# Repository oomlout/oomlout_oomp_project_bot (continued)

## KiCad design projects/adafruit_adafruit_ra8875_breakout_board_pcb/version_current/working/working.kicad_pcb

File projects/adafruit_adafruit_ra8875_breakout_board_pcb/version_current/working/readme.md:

# OOMP Project  
## Adafruit-RA8875-Breakout-Board-PCB  by adafruit  
  
oomp key: oomp_projects_flat_adafruit_adafruit_ra8875_breakout_board_pcb  
(snippet of original readme)  
  
-- Adafruit RA8875 Driver Board for 40-pin TFT Touch Displays - 800x480 Max PCB  
  
<a href="http://www.adafruit.com/products/1590"><br/>  
Click here to purchase one from the Adafruit shop</a>  
  
PCB files for the Adafruit RA8875 Driver Board for 40-pin TFT Touch Displays - 800x480 Max. Format is EagleCAD schematic and board layout  
* https://www.adafruit.com/product/1590  
  
--- Description  
  
Have you gazed longingly at large TFT displays - you know what I'm talking about here, 4", 5" or 7" TFTs with up to 800x480 pixels. Then you look at your Arduino. You love your Arduino (you really do!) but there's no way it can control a display like that, one that requires 60Hz refresh and 4 MHz pixel clocking. Heck, it doesn't even have enough pins. I suppose you could move to ARM core processors with TTL display drivers built in but you've already got all these shields working and anyways you like small micros you've got.  
  
What if I told you there was a driver chip that could fulfill those longings? A chip that can control up 800x480 displays, and heck, a resistive touchscreen as well. All you need to give up is 5 or so SPI pins. Would you even believe me? Well, sit down because this product may shock you.  
  
The RA8875 is a powerful TFT driver chip. It is a perfect match for any chip that wants to draw on a big TFT screen but doesn't quite have the oomph (whether it be hardware or speed). Inside is 768KB of RAM, so it can buffer the display (and   
  full source readme at [readme_src.md](readme_src.md)  
  
source repo at: [https://github.com/adafruit/Adafruit-RA8875-Breakout-Board-PCB](https://github.com/adafruit/Adafruit-RA8875-Breakout-Board-PCB)  
## Board  

## Schematic  

[schematic pdf](working_schematic.pdf)  
## Images

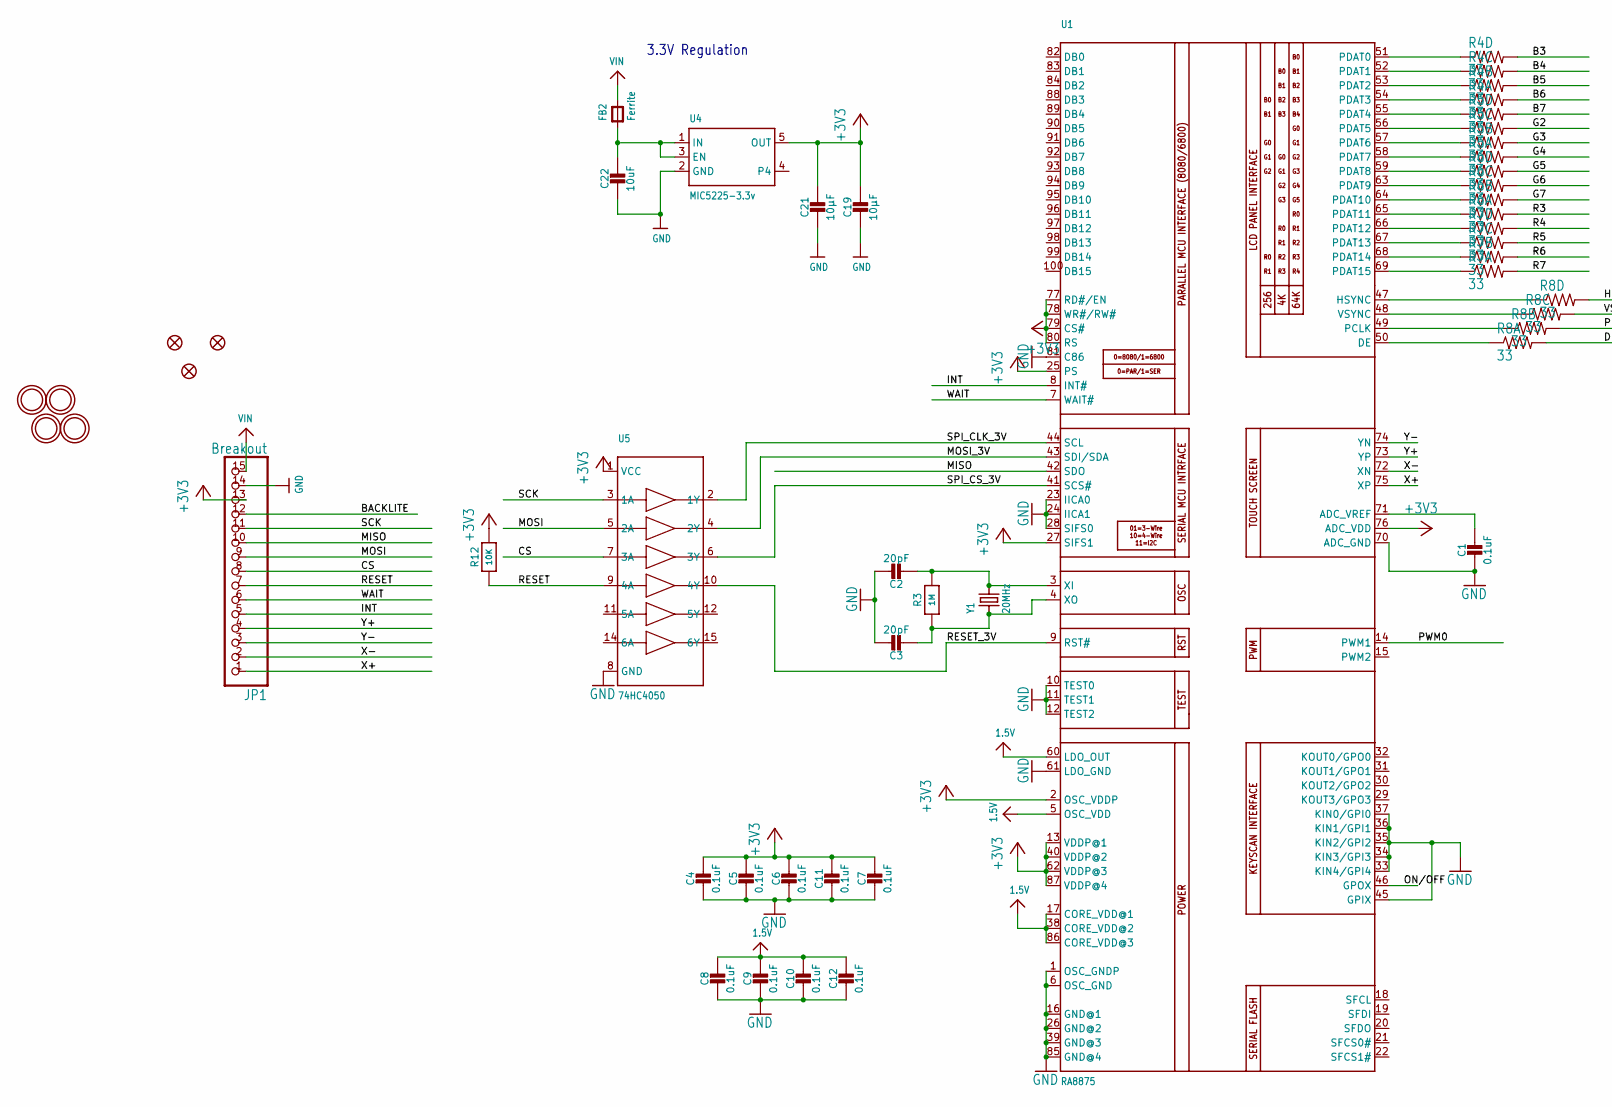
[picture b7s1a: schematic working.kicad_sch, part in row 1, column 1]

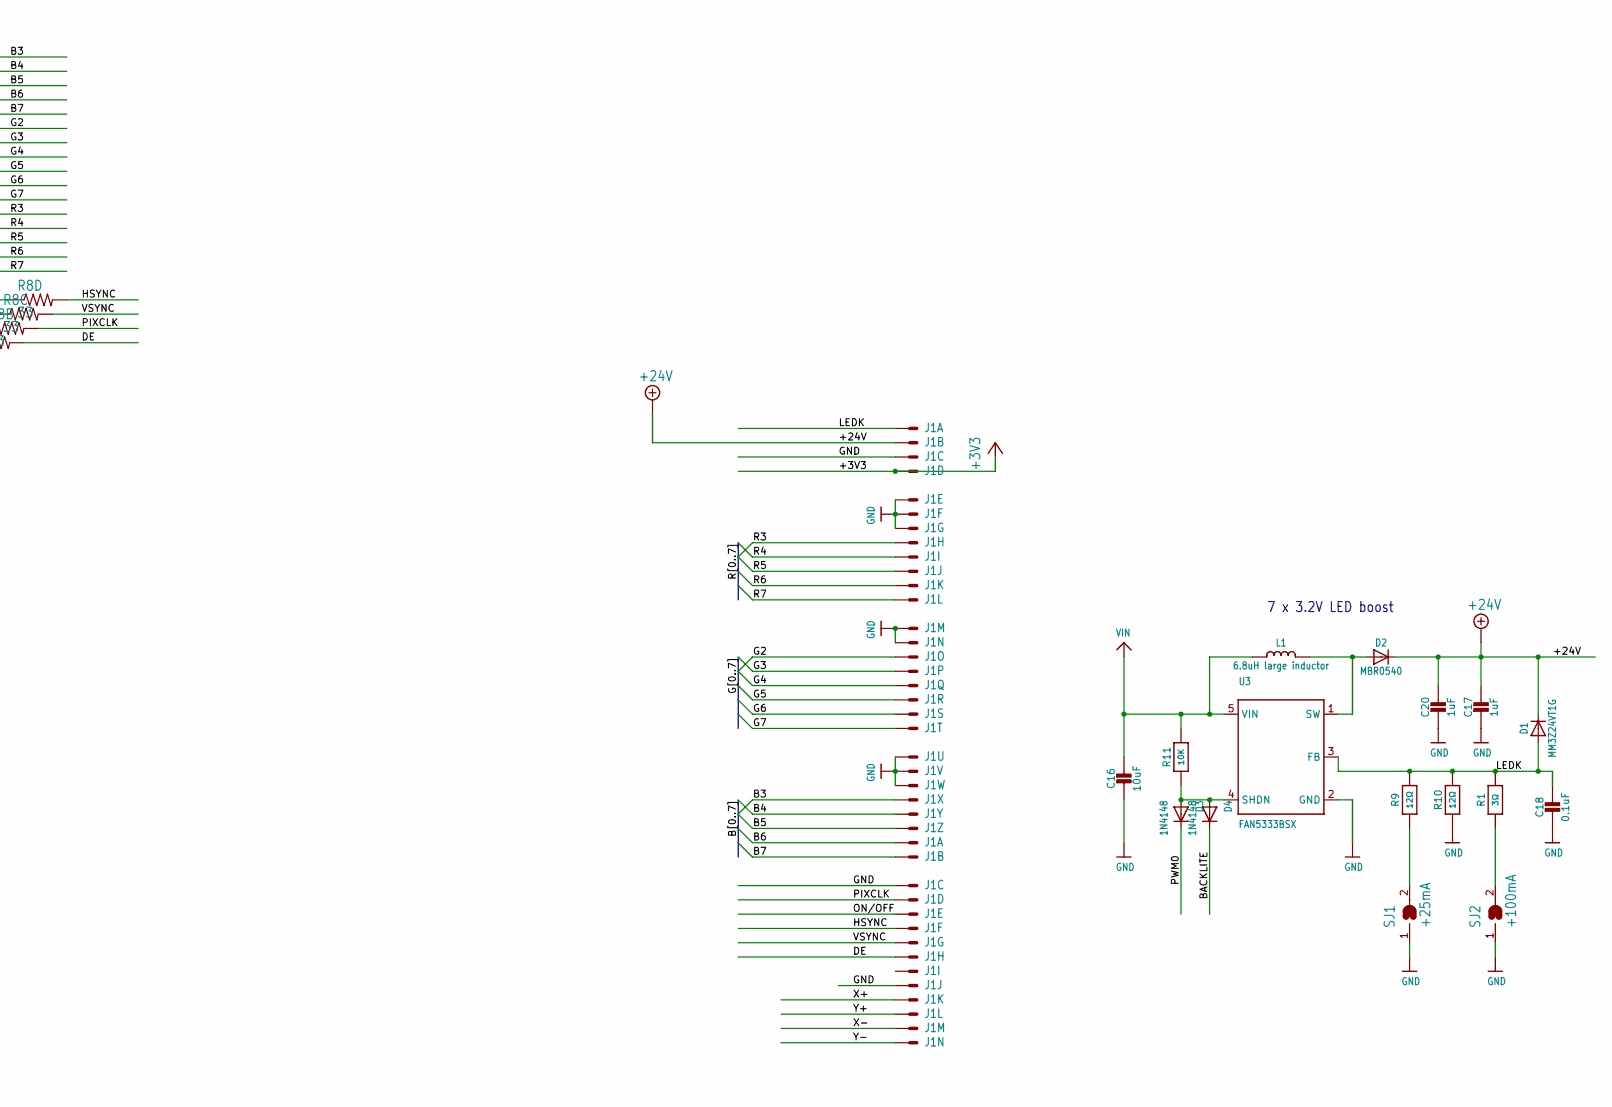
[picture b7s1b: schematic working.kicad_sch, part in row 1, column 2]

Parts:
C1, C4, C5, C6, C7, C8, C9, C10, C11, C12: 0.1uF; 0805-NO
C2, C3: 20pF; 0805-NO
C16, C22: 10uF; _0805MP
C17, C20: 1uF; _0805MP
C18: 0.1uF; _0805MP
C19, C21: 10µF; _0805MP
D1: MM3Z24VT1G; SMADIODE
D2: MBR0540; SOD-123
D3, D4: 1N4148; SOD-323F
FB2: Ferrite; _0805MP
FID1, FID2, FID3: FIDUCIAL""; FIDUCIAL_1MM
J1: 40PINFPC4-1734839-0; 4-1734839-0
JP1: Breakout; 1X15-CB
L1: 6.8uH large inductor; INDUCTOR_5X5MM_NR5040_NOTHERMALS
R1: 3Ω; _0805MP
R3: 1M; 0805-NO
R4, R5, R6, R7, R8: 33; RESPACK_4X0603
R9, R10: 12Ω; _0805MP
R11: 10K; _0805MP
R12: 10K; 0805-NO
SJ1: +25mA; SOLDERJUMPER_ARROW_NOPASTE
SJ2: +100mA; SOLDERJUMPER_ARROW_NOPASTE
U1: RA8875; LQFP100
U3: FAN5333BSX; SOT23-5@1
U4: MIC5225-3.3v; SOT23-5
U5: 74HC4050; SOIC16
U$21, U$22, U$23, U$24: MOUNTINGHOLE2.5; MOUNTINGHOLE_2.5_PLATED
Y1: 20MHz; CRYSTAL_3.2X2.5

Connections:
1.5V: C8.1, C9.1, C10.1, C12.1, U1.5 (OSC_VDD), U1.17 (CORE_VDD@1), U1.38 (CORE_VDD@2), U1.60 (LDO_OUT), U1.86 (CORE_VDD@3)
+3V3: C4.1, C5.1, C6.1, C7.1, C11.1, C19.1, C21.1, J1.4 (MS), JP1.13, R12.2, U1.2 (OSC_VDDP), U1.13 (VDDP@1), U1.25 (PS), U1.27 (SIFS1), U1.40 (VDDP@2), U1.62 (VDDP@3), U1.76 (ADC_VDD), U1.77 (RD#/EN), U1.78 (WR#/RW#), U1.79 (CS#), U1.80 (RS), U1.87 (VDDP@4), U4.5 (OUT), U5.1 (VCC)
+24V: C17.1, C20.1, D1.C, D2.C, J1.2 (MS)
B3: J1.24 (MS), R4.5 (2)
B4: J1.25 (MS), R4.6 (2)
B5: J1.26 (MS), R4.7 (2)
B6: J1.27 (MS), R4.8 (2)
B7: J1.28 (MS), R5.5 (2)
BACKLITE: D4.C, JP1.12
CS: JP1.8, U5.7 (3A)
DE: J1.34 (MS), R8.8 (2)
G2: J1.15 (MS), R5.6 (2)
G3: J1.16 (MS), R5.7 (2)
G4: J1.17 (MS), R5.8 (2)
G5: J1.18 (MS), R6.5 (2)
G6: J1.19 (MS), R6.6 (2)
G7: J1.20 (MS), R6.7 (2)
GND: C1.2, C2.1, C3.1, C4.2, C5.2, C6.2, C7.2, C8.2, C9.2, C10.2, C11.2, C12.2, C16.2, C17.2, C18.2, C19.2, C20.2, C21.2, C22.2, J1.3 (MS), J1.5 (MS), J1.6 (MS), J1.7 (MS), J1.13 (MS), J1.14 (MS), J1.21 (MS), J1.22 (MS), J1.23 (MS), J1.29 (MS), J1.36 (MS), JP1.14, R10.1, SJ1.1, SJ2.1, U1.1 (OSC_GNDP), U1.6 (OSC_GND), U1.10 (TEST0), U1.11 (TEST1), U1.12 (TEST2), U1.16 (GND@1), U1.23 (IICA0), U1.24 (IICA1), U1.26 (GND@2), U1.28 (SIFS0), U1.33 (KIN4/GPI4), U1.34 (KIN3/GPI3), U1.35 (KIN2/GPI2), U1.36 (KIN1/GPI1), U1.37 (KIN0/GPI0), U1.39 (GND@3), U1.45 (GPIX), U1.61 (LDO_GND), U1.70 (ADC_GND), U1.81 (C86), U1.85 (GND@4), U3.2 (GND), U4.2 (GND), U5.8 (GND)
HSYNC: J1.32 (MS), R8.5 (2)
INT: JP1.5, U1.8 (INT#)
LEDK: C18.1, D1.A, J1.1 (MSV), R1.2, R9.2, R10.2, U3.3 (FB)
MISO: JP1.10, U1.42 (SDO)
MOSI: JP1.9, U5.5 (2A)
MOSI_3V: U1.43 (SDI/SDA), U5.4 (2Y)
unnamed: D2.A, L1.P$2 (2), U3.1 (SW)
unnamed: C2.2, R3.2, U1.3 (XI), Y1.2
unnamed: C1.1, U1.71 (ADC_VREF)
unnamed: R4.4 (1), U1.51 (PDAT0)
unnamed: R4.3 (1), U1.52 (PDAT1)
unnamed: R4.2 (1), U1.53 (PDAT2)
unnamed: R4.1, U1.54 (PDAT3)
unnamed: R5.4 (1), U1.55 (PDAT4)
unnamed: R5.3 (1), U1.56 (PDAT5)
unnamed: R5.2 (1), U1.57 (PDAT6)
unnamed: R5.1, U1.58 (PDAT7)
unnamed: R6.4 (1), U1.59 (PDAT8)
unnamed: R6.3 (1), U1.63 (PDAT9)
unnamed: R6.2 (1), U1.64 (PDAT10)
unnamed: R6.1, U1.65 (PDAT11)
unnamed: R7.4 (1), U1.66 (PDAT12)
unnamed: R7.3 (1), U1.67 (PDAT13)
unnamed: R7.2 (1), U1.68 (PDAT14)
unnamed: R7.1, U1.69 (PDAT15)
unnamed: R8.1, U1.50 (DE)
unnamed: R8.2 (1), U1.49 (PCLK)
unnamed: R8.3 (1), U1.48 (VSYNC)
unnamed: R8.4 (1), U1.47 (HSYNC)
unnamed: R9.1, SJ1.2
unnamed: C22.1, FB2.1, U4.1 (IN), U4.3 (EN)
unnamed: R1.1, SJ2.2
unnamed: C3.2, R3.1, U1.4 (XO), Y1.1
ON/OFF: J1.31 (MS), U1.46 (GPOX)
PIXCLK: J1.30 (MS), R8.7 (2)
PWM0: D3.C, U1.14 (PWM1)
R3: J1.8 (MS), R6.8 (2)
R4: J1.9 (MS), R7.5 (2)
R5: J1.10 (MS), R7.6 (2)
R6: J1.11 (MS), R7.7 (2)
R7: J1.12 (MS), R7.8 (2)
RESET: JP1.7, R12.1, U5.9 (4A)
RESET_3V: U1.9 (RST#), U5.10 (4Y)
SCK: JP1.11, U5.3 (1A)
SHDN: D3.A, D4.A, R11.1, U3.4 (SHDN)
SPI_CLK_3V: U1.44 (SCL), U5.2 (1Y)
SPI_CS_3V: U1.41 (SCS#), U5.6 (3Y)
VIN: C16.1, FB2.2, JP1.15, L1.P$1 (1), R11.2, U3.5 (VIN)
VSYNC: J1.33 (MS), R8.6 (2)
WAIT: JP1.6, U1.7 (WAIT#)
X+: J1.37 (MS), JP1.1, U1.75 (XP)
X-: J1.39 (MS), JP1.2, U1.72 (XN)
Y+: J1.38 (MS), JP1.4, U1.73 (YP)
Y-: J1.40 (MS), JP1.3, U1.74 (YN)

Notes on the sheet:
3.3V Regulation
7 x 3.2V LED boost

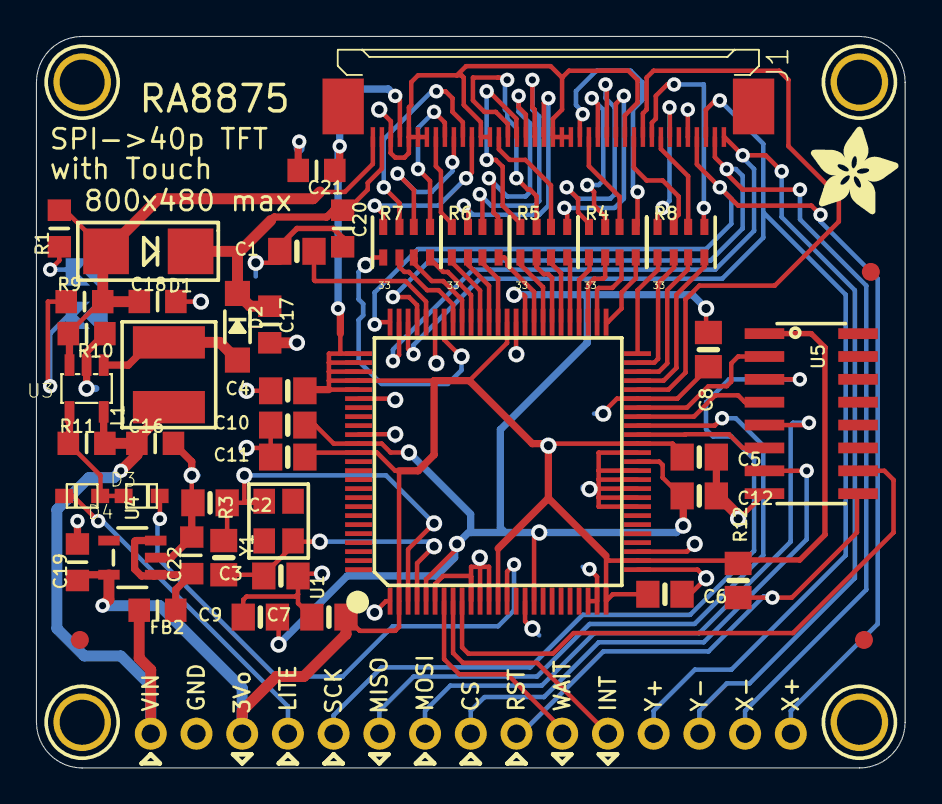
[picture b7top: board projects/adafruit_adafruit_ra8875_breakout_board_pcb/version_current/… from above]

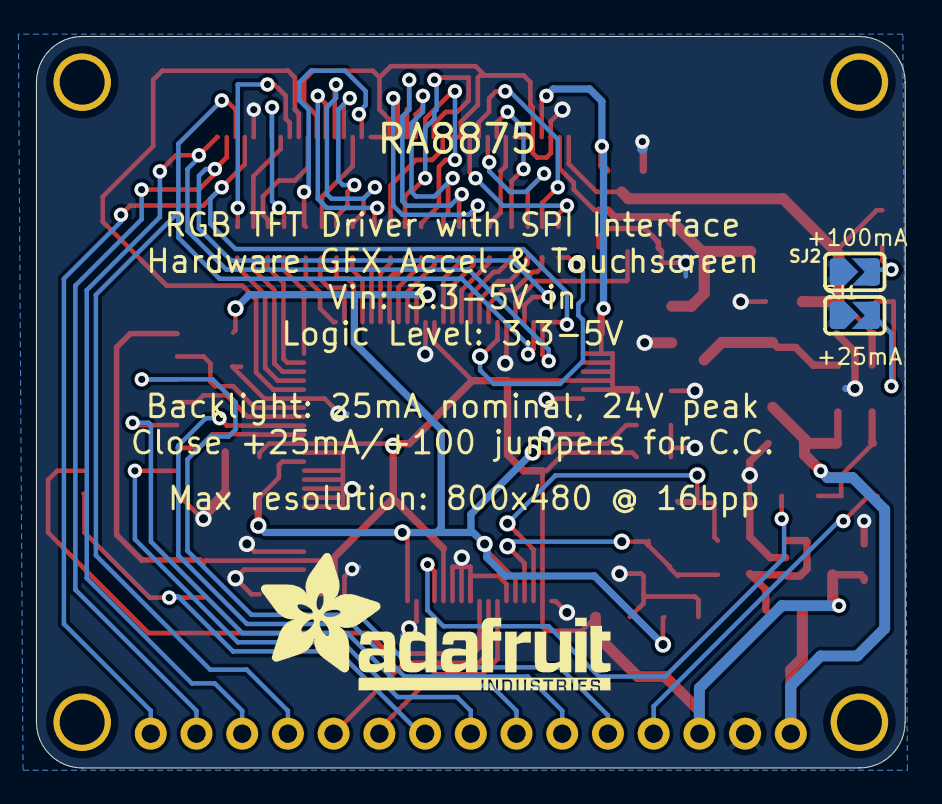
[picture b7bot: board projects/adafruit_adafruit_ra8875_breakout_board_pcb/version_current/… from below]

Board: 2 copper layers, 48.3 x 40.6 mm, 54 parts (3 on the bottom side), 72 nets.

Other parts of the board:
U$18: ADAFRUIT_5MM
U$25: ADAFRUIT_TEXT_20MM

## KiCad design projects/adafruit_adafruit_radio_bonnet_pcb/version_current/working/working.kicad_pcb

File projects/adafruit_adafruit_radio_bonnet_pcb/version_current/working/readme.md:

# OOMP Project  
## Adafruit-Radio-Bonnet-PCB  by adafruit  
  
oomp key: oomp_projects_flat_adafruit_adafruit_radio_bonnet_pcb  
(snippet of original readme)  
  
-- Adafruit LoRa Radio Bonnet with OLED - RFM95W @ 915MHz - RadioFruit PCB  
  
<a href="http://www.adafruit.com/products/4074"><br/>  
Click here to purchase one from the Adafruit shop</a>  
  
PCB files for the Adafruit LoRa Radio Bonnet with OLED - RFM95W @ 915MHz - RadioFruit. Format is EagleCAD schematic and board layout  
* https://www.adafruit.com/product/4074  
  
--- Description  
  
The latest Raspberry Pi computers come with WiFi and Bluetooth, and now you can add even more radio options with the Adafruit Radio Bonnets! Upgrade your Raspberry Pi with a LoRa / LoRaWAN radio, so it can communicate over very long distances. These bonnets plug right into your Pi and give you long range wireless capabilities to remote nodes that may be battery powered. Or, you can create Internet gateways with ease.  
  
You not only get a radio module, but also a 128x32 OLED display for status messages and three buttons you can use for creating a custom user interface or sending test messages. All of the above is supported with our Python libraries so you can send or receive LoRa data with other matching modules, send data to a LoRaWAN gateway, or even set up your own single channel LoRaWAN-to-Internet gateways.  
  
Compared to the 2.4 GHz WiFi/Bluetooth radios on the Pi already, these modules run at 433 or 900 MHz (sub-GHz). You can't send data as fast but you can send data a lot farther. These packet radios are simpler than WiFi or BLE, you don't have to associ  
  full source readme at [readme_src.md](readme_src.md)  
  
source repo at: [https://github.com/adafruit/Adafruit-Radio-Bonnet-PCB](https://github.com/adafruit/Adafruit-Radio-Bonnet-PCB)  
## Board  

## Schematic  

[schematic pdf](working_schematic.pdf)  
## Images

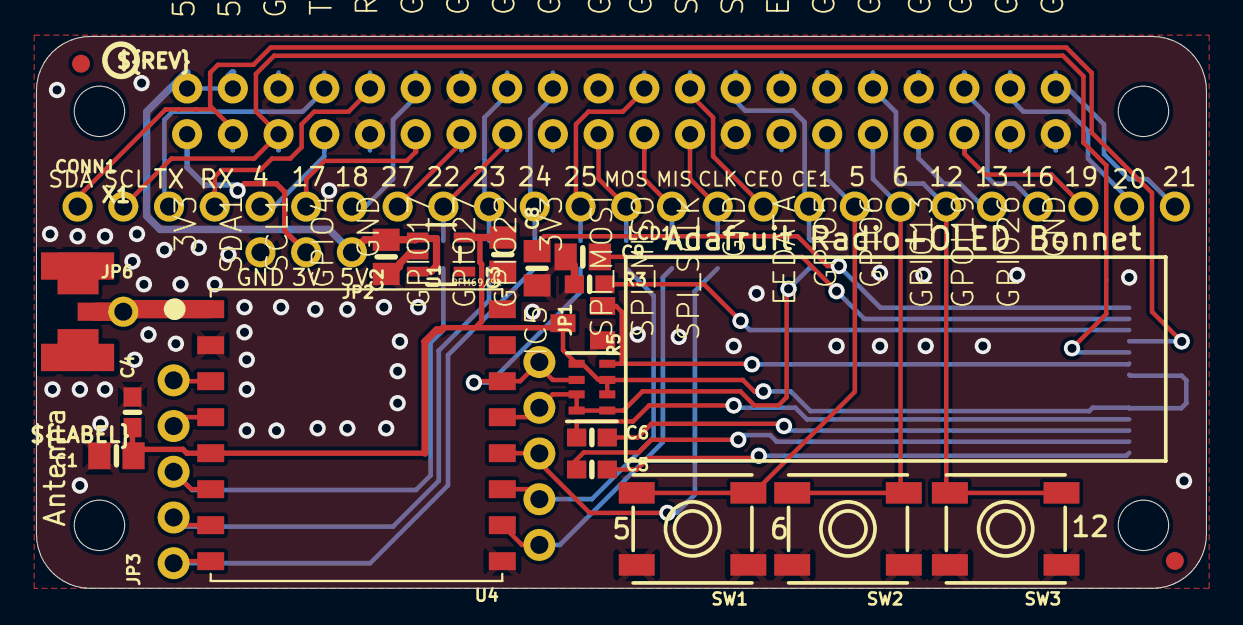
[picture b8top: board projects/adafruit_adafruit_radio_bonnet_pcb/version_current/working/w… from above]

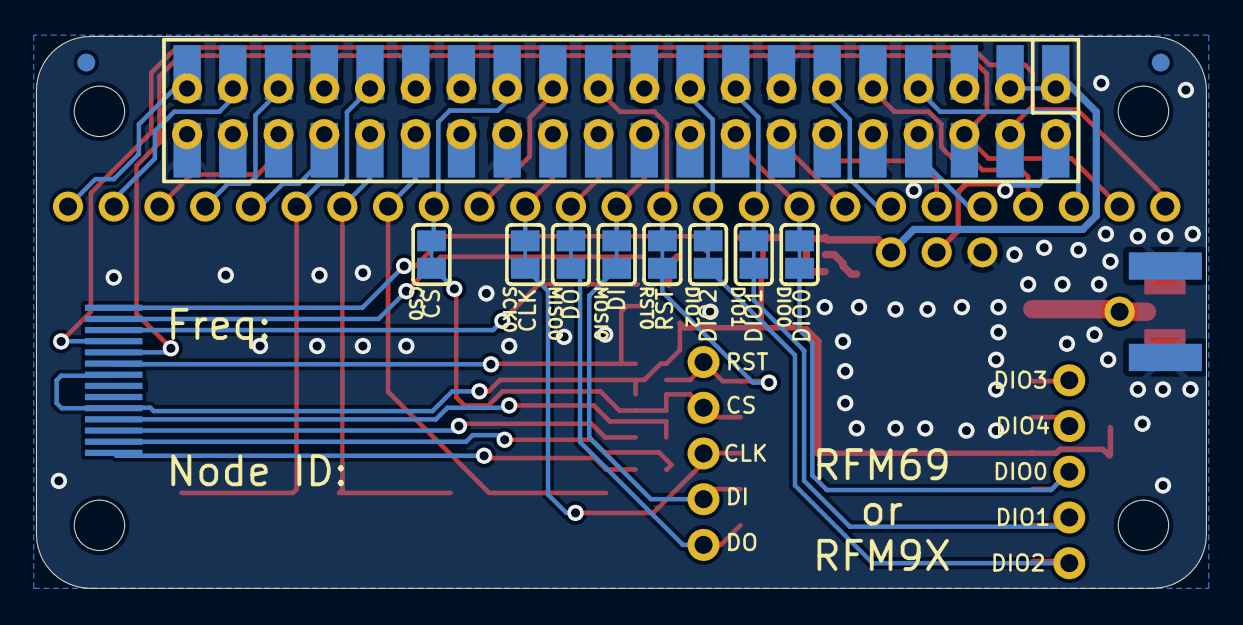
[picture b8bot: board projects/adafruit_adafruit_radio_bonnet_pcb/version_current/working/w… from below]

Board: 2 copper layers, 65.0 x 30.7 mm, 35 parts (8 on the bottom side), 52 nets.

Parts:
C1, C2, C3, C8, C9: 10uF; 0805-NO
C4: 0.1uF; 0603-NO
C5, C6: 1uF; 0603-NO
CONN1: HEADER-1X25; 1X25_ROUND_70MIL
CS0: SOLDERJUMPER_CLOSEDWIRE
DIO0, DIO1, DIO2: SOLDERJUMPER_CLOSEDWIRE
FID1, FID2: FIDUCIAL_1MM
IC5: APX803; SOT23
JP1, JP3: 1X05_ROUND_70
JP2: 1X03_ROUND
JP6: 1X01_ROUND
LCD1: OLED 128x32; UG-2832HSWEG02_WRAPUNDER
MISO0: SOLDERJUMPER_CLOSEDWIRE
MOSI0: SOLDERJUMPER_CLOSEDWIRE
R3: 390K; 0603-NO
R5: 10K; RESPACK_4X0603
RPI1: RASPBERRYPI_BPLUS_BONNET_THMSMT; PI_BONNET_THMSMT
RST0: SOLDERJUMPER_CLOSEDWIRE
SCK0: SOLDERJUMPER_CLOSEDWIRE
SW1, SW2, SW3: 6mm; EVQ-Q2_SMALLER
U1: AP2112K-3.3; SOT23-5
U4: RFM69/9x; RFMHCW_SMT
U$22: PCBFEAT-REV-040
X1: uFL/SMA; SMA_EDGELAUNCH_UFL

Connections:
3.3V: C1.1, C3.1, C4.1, IC5.3, LCD1.5, LCD1.8, R5.1, R5.6, R5.7, U1.5, U4.5P
5.0V: C2.1, JP2.1, RPI1.2, RPI1.4, RPI1.S2, RPI1.S4, U1.1, U1.3
ANT: JP6.1, U4.1P, X1.P
DIO0: DIO0.1, JP3.3, U4.6P
DIO1: DIO1.1, JP3.2, U4.7P
DIO2: DIO2.1, JP3.1, U4.8P
DIO3: JP3.5, U4.3P
DIO4: JP3.4, U4.4P
EECLK: RPI1.28, RPI1.S28
EEDATA: RPI1.27, RPI1.S27
GND: C1.2, C2.2, C3.2, C4.2, C8.1, C9.1, IC5.1, JP2.3, LCD1.7, R3.1, RPI1.6, RPI1.9, RPI1.14, RPI1.20, RPI1.25, RPI1.30, RPI1.34, RPI1.39, RPI1.S6, RPI1.S9, RPI1.S14, RPI1.S20, RPI1.S25, RPI1.S30, RPI1.S34, RPI1.S39, SW1.B, SW1.B', SW2.B, SW2.B', SW3.B, SW3.B', U1.2, U4.2P, U4.9P, U4.16P, X1.GND@1, X1.GND@2, X1.GND@3, X1.GND@4
GPIO4: CONN1.5, RPI1.7, RPI1.S7
GPIO5: CONN1.18, RPI1.29, RPI1.S29, SW1.A, SW1.A'
GPIO6: CONN1.19, RPI1.31, RPI1.S31, SW2.A, SW2.A'
GPIO12: CONN1.20, RPI1.32, RPI1.S32, SW3.A, SW3.A'
GPIO13: CONN1.21, RPI1.33, RPI1.S33
GPIO16: CONN1.22, RPI1.36, RPI1.S36
GPIO17: CONN1.6, RPI1.11, RPI1.S11
GPIO18: CONN1.7, RPI1.12, RPI1.S12
GPIO19: CONN1.23, RPI1.35, RPI1.S35
GPIO20: CONN1.24, RPI1.38, RPI1.S38
GPIO21: CONN1.25, RPI1.40, RPI1.S40
GPIO22: CONN1.9, DIO0.2, RPI1.15, RPI1.S15
GPIO23: CONN1.10, DIO1.2, RPI1.16, RPI1.S16
GPIO24: CONN1.11, DIO2.2, RPI1.18, RPI1.S18
GPIO25: CONN1.12, RPI1.22, RPI1.S22, RST0.2
GPIO26: RPI1.37, RPI1.S37
GPIO27: CONN1.8, RPI1.13, RPI1.S13
unnamed: C5.2, LCD1.1
unnamed: C5.1, LCD1.2
unnamed: C6.2, LCD1.3
unnamed: C6.1, LCD1.4
unnamed: LCD1.12, R3.2
RFM_CS: CS0.1, JP1.2, R5.3, R5.4, R5.5, U4.13P
RFM_MISO: JP1.5, MISO0.1, U4.10P
RFM_MOSI: JP1.4, MOSI0.1, U4.11P
RFM_RST: JP1.1, R5.2, RST0.1, U4.14P
RFM_SCK: JP1.3, SCK0.1, U4.12P
RPI_3.3V: JP2.2, RPI1.1, RPI1.S1
RPI_3.3V@2: RPI1.17, RPI1.S17
RXD: CONN1.4, RPI1.10, RPI1.S10
SCL: CONN1.2, LCD1.10, RPI1.5, RPI1.S5
SDA: CONN1.1, LCD1.11, RPI1.3, RPI1.S3
SPI_CE0: CONN1.16, RPI1.24, RPI1.S24
SPI_CE1: CONN1.17, CS0.2, RPI1.26, RPI1.S26
SPI_MISO: CONN1.14, MISO0.2, RPI1.21, RPI1.S21
SPI_MOSI: CONN1.13, MOSI0.2, RPI1.19, RPI1.S19
SPI_SCLK: CONN1.15, RPI1.23, RPI1.S23, SCK0.2
TXD: CONN1.3, RPI1.8, RPI1.S8
VCC: C8.2, LCD1.14
VCOMH: C9.2, LCD1.13
~OLED_RST: IC5.2, LCD1.9, R5.8
